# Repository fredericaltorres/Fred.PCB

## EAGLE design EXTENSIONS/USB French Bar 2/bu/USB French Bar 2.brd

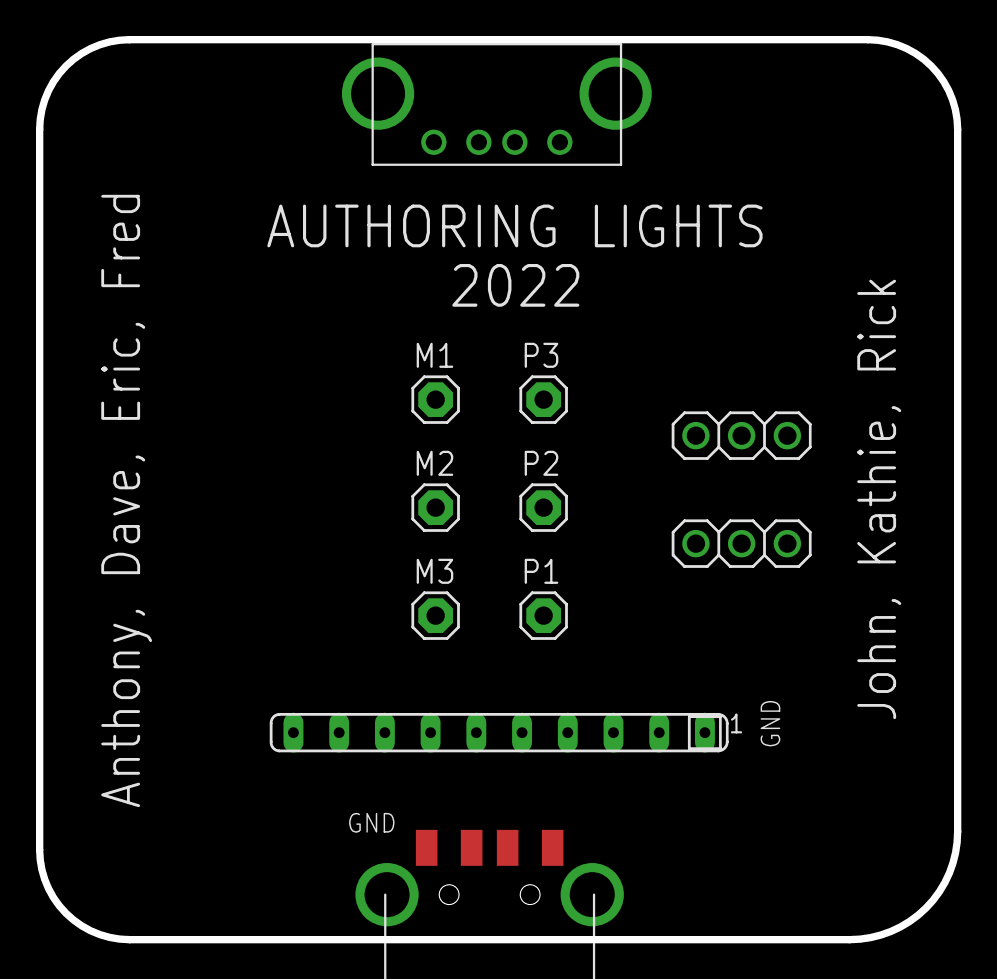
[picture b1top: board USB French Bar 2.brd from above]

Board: 2 copper layers, 51.0 x 50.0 mm, 11 parts (0 on the bottom side), 8 nets, no tracks yet.

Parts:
JP1, JP3: 1X03
M1, M2, M3: 1X01
P1, P2, P3: 1X01
RN1: SIP10
U$1: USB; USB-FEMALE-A-PTH
X1: USB-A; MOLEX_480371000

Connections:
unnamed: RN1.1, U$1.GND, X1.4
unnamed: M1.1, RN1.10
unnamed: U$1.D+, X1.3
unnamed: U$1.D-, X1.2
unnamed: M2.1, RN1.8
unnamed: M3.1, RN1.4
unnamed: JP1.2, P1.1, P2.1, P3.1
VCC: JP1.1, U$1.VBUS, X1.1

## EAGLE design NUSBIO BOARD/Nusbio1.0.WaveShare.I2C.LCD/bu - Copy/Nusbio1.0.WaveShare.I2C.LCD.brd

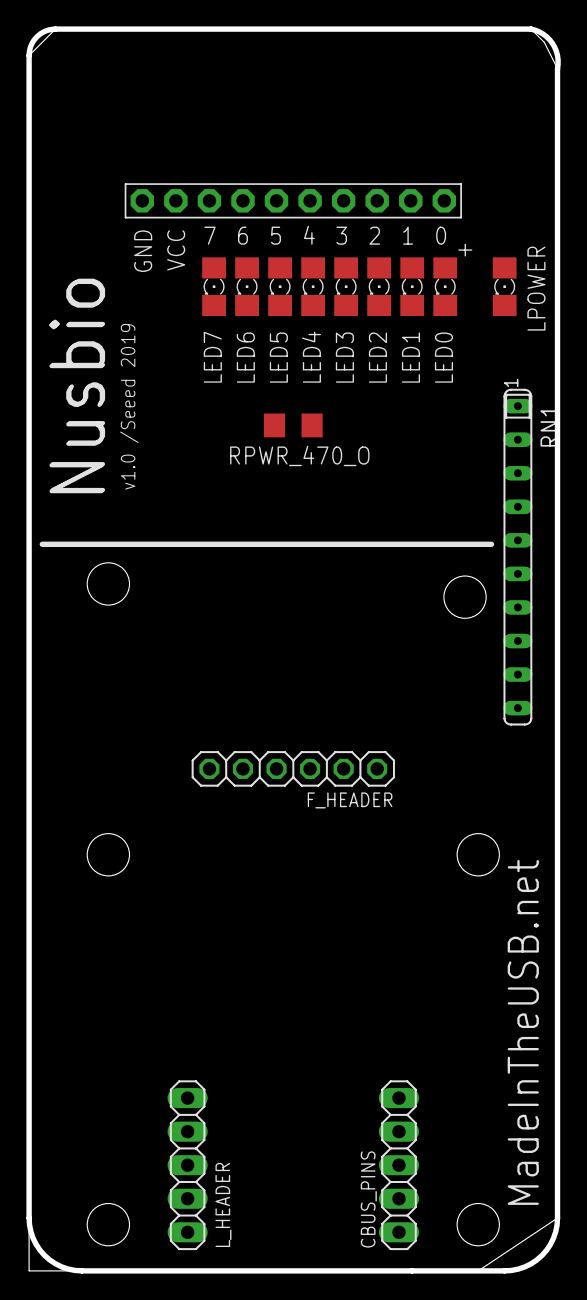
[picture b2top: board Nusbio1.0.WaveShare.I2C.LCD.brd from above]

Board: 2 copper layers, 40.0 x 94.0 mm, 15 parts (0 on the bottom side), 19 nets, no tracks yet.

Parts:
CBUS_PINS: 1X05
F_HEADER: 1X06
LED0, LED1, LED2, LED3, LED4, LED5, LED6, LED7: 1206
LPOWER: 1206
L_HEADER: 1X05
RN1: SIP10
RPWR_470_O: R1206
U$1: PINHD-1X10; 1X10-BIG

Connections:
CTS_G4: F_HEADER.6, LED4.A, U$1.5
DCD_G3: LED3.A, L_HEADER.2, U$1.4
DSR_G1: LED1.A, L_HEADER.3, U$1.2
DTR_G2: LED2.A, L_HEADER.5, U$1.3
GND: F_HEADER.2, RN1.1, RPWR_470_O.2, U$1.10
unnamed: LED1.C, RN1.3
unnamed: LED0.C, RN1.2
unnamed: LED2.C, RN1.4
unnamed: LED3.C, RN1.5
unnamed: LED4.C, RN1.6
unnamed: LED7.C, RN1.9
unnamed: LED5.C, RN1.7
unnamed: LED6.C, RN1.8
unnamed: LPOWER.C, RPWR_470_O.1
NUSBIO_VCC: F_HEADER.1, LPOWER.A, U$1.9
RI_G0: LED0.A, L_HEADER.4, U$1.1
RTS_G7: F_HEADER.5, LED7.A, U$1.8
RX_G6: F_HEADER.4, LED6.A, U$1.7
TX_G5: F_HEADER.3, LED5.A, U$1.6
